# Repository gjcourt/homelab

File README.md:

<!-- readme-type: infra -->
# Homelab

GitOps for a 4-node Talos Kubernetes homelab cluster, reconciled by Flux CD

Running a cluster by hand invites config drift and leaves no record of what
changed or why. This repo is the single source of truth for the
`melodic-muse` Talos cluster: every app, controller, and cluster config lives
here as a Kustomize base, overlay, or Helm release. Flux CD reconciles
`master` into the cluster on a 10-minute interval (or on demand), so a merged
PR is the only way anything reaches production.

**Status:** in daily use — this is the live source of truth for the
`melodic-muse` cluster; Flux reconciles `master` continuously, with commits
landing as recently as 2026-09-29.

## Layout

```text
apps/       Kustomize bases + staging/production overlays, one directory per app
infra/      controllers (HelmReleases) and the configs they depend on
clusters/   Flux Kustomization entrypoints
hosts/      compose files, scripts, and docs for hosts outside Kubernetes (hestia, alcatraz, ...)
images/     Dockerfiles for the images this repo builds and publishes to ghcr.io
firmware/   ESPHome configs for IR blasters and sensors
docs/       architecture, runbooks, plans, incident postmortems
scripts/    repo maintenance and host-ops tooling
renovate/   Renovate dependency-update config
```

Current app and infra inventory: [apps/README.md](apps/README.md),
[infra/README.md](infra/README.md). Current cluster state, in-flight work, and
known issues: [docs/STATUS.md](docs/STATUS.md).

## Making a change

1. Branch from `master`: `git checkout master && git pull && git checkout -b <type>/<description>`.
2. Edit `apps/`, `infra/`, `docs/`, or `scripts/`, and validate locally (see Development below).
3. Push and open a PR. CI rebuilds the `staging` branch (`master` plus every
   open, mergeable PR whose checks pass) and deploys it to the `-stage` namespaces, so you can check the
   change against the real cluster before it merges.
4. Merging to `master` deploys to production on Flux's next reconcile, or
   force it with `flux reconcile kustomization apps-production -n flux-system`.

Secrets are SOPS-encrypted before commit and decrypted in-cluster by Flux;
never commit a plaintext secret. Full walkthrough, including adding a new app
and rolling back:
[docs/operations/making-changes.md](docs/operations/making-changes.md).

## Development

```bash
make test                                    # kustomize build + kubeconform (apps/staging, apps/production, infra/*) + yamlfmt check
make lint                                    # yamllint (.yamllint) + shellcheck on scripts/*.sh
(cd scripts/plans-index && go run . -check)  # verify docs/plans frontmatter matches the generated index
```

Conventions, invariants, and the full command reference:
[AGENTS.md](AGENTS.md).

## License

[MIT](LICENSE)

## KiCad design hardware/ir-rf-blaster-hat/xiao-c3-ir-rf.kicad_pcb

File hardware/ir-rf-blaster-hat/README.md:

# XIAO ESP32-C3 IR + RF Blaster Hat — 4-layer, routed

A XIAO-carrier "hat": the XIAO ESP32-C3 sockets into female headers (Seeed's **official
XIAO-ESP32-C3-DIP** footprint); the board carries a **triple-IR-LED blaster** (MOSFET-driven)
**and a CC1101 sub-GHz RF transmitter** (TX-only). IR LEDs are THT (hand-soldered, better
range); everything else SMD for JLCPCB assembly. The CC1101 is a socketed **EBYTE E07-M1101D**
module.

**Status (2026-07-14): 4-layer, fully routed, DRC-clean, fab-ready.** Generated headlessly
(`generate_pcb.py`, kiutils) + zone-filled + validated with `kicad-cli` (KiCad 9): **DRC 0
errors, 0 unconnected**. Board is **23 × 54 mm**. Gerbers/drill in
[`ir-rf-gerbers.zip`](ir-rf-gerbers.zip); renders [`ir-rf-top.png`](ir-rf-top.png) /
[`ir-rf-bottom.png`](ir-rf-bottom.png); module orientation [`e07-orientation.svg`](e07-orientation.svg).

## Floorplan

```
        NORTH (top)
   ┌──────────────────┐
   │  D1   D2   D3     │  3× 940 nm IR LED (THT), aimed north/off the top edge
   │  R  Q1  R   caps  │  MOSFET driver row
   │ ┌──────────────┐  │
USB┤ │ XIAO (front) │  │  XIAO horizontal — USB-C exits the WEST edge
   │ └──────────────┘  │
   │   [E07 on BACK]   │  E07-M1101D on a 2×4 female socket, flipped to B.Cu;
   │        ││         │  15×30 mm module body lies over the XIAO back and
   │        ▼▼         │  extends SOUTH — SMA/antenna off the south edge.
   └────────╨╨────────┘
        SOUTH (antenna)
```

- **XIAO** is on the **front** (Seeed official XIAO-ESP32-C3-DIP footprint), rotated horizontal
  (rot 180) so **USB-C exits the west edge**; the two 7-pin rows run E-W, **15.24 mm apart**
  (real Seeed pitch). NORTH row = 5V/GND/3V3 + D10/D9/D8/D7; SOUTH row = D0–D6.
- **E07-M1101D CC1101** is on the **back**, on a **swappable 2×4 female socket**. Per the
  CDEBYTE datasheet the 2×4 header runs **4-across the module's 15 mm width**; the 30 mm body
  + SMA connector extend perpendicular to it, so with the header at the north end the
  **antenna points south, off the board edge**. An **all-layer copper keepout** clears the
  planes under the RF/antenna region (y 46–54).

## Frequency & the swappable socket

The **CC1101 chip** is multi-band (300–348 / 387–464 / 779–928 MHz), but any physical
**module** is impedance-matched + antenna-tuned to **one** band. The **E07-M1101D is a 433 MHz
module** (covers ~387–464 MHz) — the common band for US/EU fixed-code outlets, doorbells, many
fan remotes. 315 MHz gear (some garage openers/older remotes) or 868/915 MHz needs a
differently-tuned module.

The board is deliberately **band-agnostic**: the CC1101 slot is a plain 8-pin 2×4 socket, so
any same-pinout CC1101 module (or an SMA E07 with a swapped antenna) drops in. Pick the module
for your band; the PCB doesn't change.

## Stackup (4-layer)

| Layer      | Use                                                       |
| ---------- | --------------------------------------------------------- |
| **F.Cu**   | components + signals (IR section, N-row SPI, +3V3)         |
| **In1.Cu** | **GND plane** (solid) — clean return for the IR pulses    |
| **In2.Cu** | **+5V plane** — LED current                               |
| **B.Cu**   | signals (S-row SPI, GDO2 dogleg, gate)                    |

GND and +5V go to their planes via stitching vias (through-vias; the opposite plane's zone
clears around each). Only `+3V3` and the logic signals are routed as tracks. The E07 socket's
GND/VCC pins are THT and land directly on the planes.

## Pin maps

**XIAO ESP32-C3** (official pad numbers) — the E07 **north row** (odd pins, datasheet order)
fans from the XIAO **north** row; the **south row** (even pins) from the XIAO **south** row.
`MISO` is the one north-row net fed from the south (a clean east-side dogleg). **All three
strapping pins are left spare** — D0/GPIO2 (pad 1), D8/GPIO8 (pad 9), D9/GPIO9 (pad 10). `IR_TX`
is on **D1/GPIO3** (non-strapping): D0 was avoided because the 10 kΩ gate pulldown would drag
GPIO2 low at reset (~0.6 V through the ~45 kΩ internal pull-up), against ESP32-C3 guidance.

| Net      | XIAO pin | GPIO | pad # | → E07 pin      |
| -------- | -------- | ---- | ----- | -------------- |
| IR_TX    | D1       | 3    | 2     | (to MOSFET)    |
| CC_GDO0  | D10      | 10   | 11    | 3 (N row)      |
| CC_SCK   | D7       | 20   | 8     | 5 (N row)      |
| CC_MISO  | D6       | 21   | 7     | 7 (N, dogleg)  |
| CC_CSN   | D2       | 4    | 3     | 4 (S row)      |
| CC_MOSI  | D3       | 5    | 4     | 6 (S row)      |
| CC_GDO2  | D4       | 6    | 5     | 8 (S row)      |
| +3V3     | 3V3      | —    | 12    | 2 (VCC)        |
| GND      | GND      | —    | 13    | 1              |
| +5V      | VBUS     | —    | 14    | —              |

Power: IR LEDs → **5V (VBUS)**; CC1101 → **3V3**; common GND. D0/D5/D8/D9 (pads 1/6/9/10) spare.

**Hand-solder polarity (THT):**
- **D1–D3 IR LEDs** — footprint **pad 1 (square, west, flat-silk side) = CATHODE**; pad 2
  (round, east) = anode = +5 V. Solder each LED with its **flat / short lead (cathode) to the
  square pad**. (The cathode goes to the current-limit resistor → MOSFET; the anode to +5 V.)
- **A1 XIAO** and **M1 E07** — keyed by pad 1 (square) on their footprints; match pin 1.

**E07-M1101D socket (M1, 2×4 female)** — **fixed CDEBYTE pinout**, the module plugs straight in:

```
  1 GND    2 VCC(3V3)
  3 GDO0   4 CSN
  5 SCK    6 MOSI
  7 MISO   8 GDO2
```

> ⚠️ E07 logic is **3.3 V** — the datasheet warns 5 V TTL "may be at risk of burning down."
> The XIAO drives it at 3.3 V; keep it off VBUS.

## BOM

| Ref     | Part                | Value/MPN            | Pkg    | Mount | Footprint                  |
| ------- | ------------------- | -------------------- | ------ | ----- | -------------------------- |
| Q1      | N-ch MOSFET         | AO3400A (C20917)     | SOT-23 | SMT   | `SOT-23`                   |
| D1–D3   | 940 nm IR LED       | TSAL6400             | 5 mm   | THT   | `LED_D5.0mm`               |
| R1–R3   | Res (LED limit)     | 15 Ω                 | 1206   | SMT   | `R_1206_3216Metric`        |
| R4      | Res (gate)          | 100 Ω                | 0603   | SMT   | `R_0603_1608Metric`        |
| R5      | Res (pulldown)      | 10 kΩ                | 0603   | SMT   | `R_0603_1608Metric`        |
| C1,C3   | Cap                 | 100 nF               | 0603   | SMT   | `C_0603_1608Metric`        |
| C2      | Cap (IR bulk)       | 22 µF                | 0805   | SMT   | `C_0805_2012Metric`        |
| C4      | Cap (RF bulk)       | 10 µF                | 0805   | SMT   | `C_0805_2012Metric`        |
| M1      | **E07-M1101D** hdr  | 2×4 socket, 2.54 mm  | THT    | hand  | `PinSocket_2x04_P2.54mm`   |
| A1      | XIAO ESP32-C3 socket| 2×7 female, 2.54 mm  | THT    | hand  | `XIAO-ESP32-C3-DIP` (Seeed)|

Module (not on the PCB BOM): **EBYTE E07-M1101D** (or E07-M1101D-SMA for an external antenna),
433 MHz, LCSC C108549 / Amazon.

## Before ordering (KiCad GUI)

- **Footprint:** now Seeed's official `XIAO-ESP32-C3-DIP` (15.24 mm rows) — the footprint's own
  silk is stripped in the generator (it overhangs the USB end and crosses its castellated pads);
  pads + our labels remain.
- **Back-side stack (confirmed OK):** the E07 socket pins protrude ~1 mm through-hole under the
  XIAO — clears fine. The 30 mm module body overhangs the south edge slightly; the SMA/antenna
  sits in free air beyond the board.
- Optional: a final 3D view before fab.

## Regenerate / validate / order (headless)

```sh
# 1. generate the board (native, kiutils) - writes zones UNFILLED
python3 generate_pcb.py footprints xiao-c3-ir-rf.kicad_pcb

# 2. fill zones + validate + export (KiCad 9; amd64 image on Apple Silicon)
docker run --rm --platform linux/amd64 -v "$PWD:/w" -w /w kicad/kicad:9.0 sh -c '
  python3 /w/fill_zones.py xiao-c3-ir-rf.kicad_pcb xiao-c3-ir-rf.kicad_pcb
  kicad-cli pcb drc xiao-c3-ir-rf.kicad_pcb
  kicad-cli pcb export gerbers -o g/ xiao-c3-ir-rf.kicad_pcb
  kicad-cli pcb export drill   -o g/ xiao-c3-ir-rf.kicad_pcb'
```

> **Toolchain note:** `pcbnew` Python scripting crashes under amd64 emulation on Apple Silicon
> in `FootprintLoad` (`malloc(): unaligned tcache chunk`) — so the board is *generated* with
> **kiutils** (native, pure-Python) and *zone-filled* with **`pcbnew.LoadBoard`** (which does
> NOT crash), then `kicad-cli` runs DRC/export. `footprints/` holds the KiCad-9 footprints the
> generator places (offline-reproducible).
>
> One headless gotcha baked into the generator: kicad-cli places a **B.Cu** THT footprint's
> pads at the plain rotated local coords (no X-mirror), so `abspad()` must **not** mirror — the
> E07 even/odd pins land on the south/north rows accordingly.

## Firmware (ESPHome)

`../../firmware/esphome/ir-rf-blaster-xiao-c3.yaml`: `remote_transmitter` (IR) — note IR_TX is
now **GPIO3 (D1)** (was GPIO4); update the YAML pin. The CC1101 needs an **external component**
(SPI init + GDO0 OOK bridge) — a known community pattern, not stock ESPHome. Match the pin map
above: **SCK=GPIO20, MISO=GPIO21, MOSI=GPIO5, CSN=GPIO4, GDO0=GPIO10, GDO2=GPIO6**.

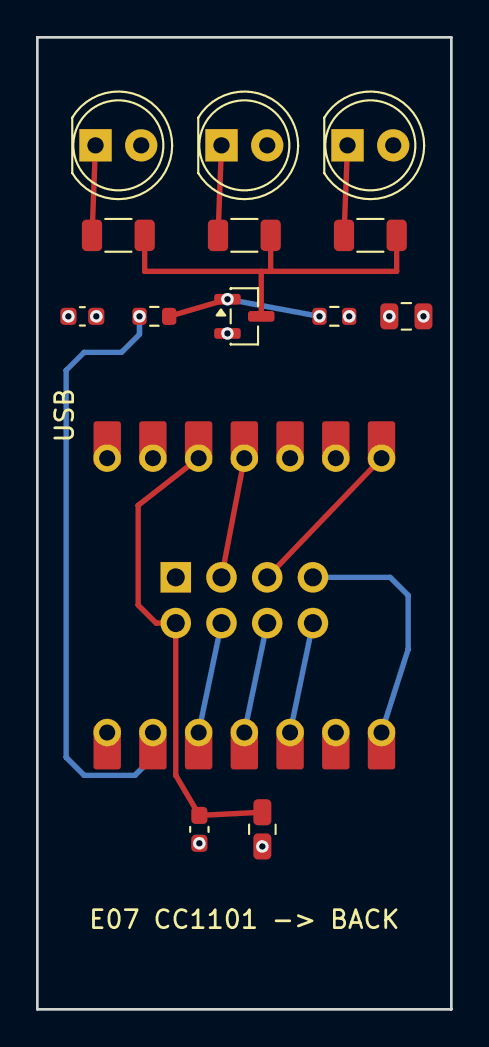
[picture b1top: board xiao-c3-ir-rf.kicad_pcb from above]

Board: 4 copper layers, 23.0 x 54.0 mm, 15 parts (1 on the bottom side), 15 nets.

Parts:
A1: XIAO_ESP32C3; XIAO-ESP32-C3-DIP
C1, C3: 100nF; C_0603_1608Metric
C2: 22uF; C_0805_2012Metric
C4: 10uF; C_0805_2012Metric
D1, D2, D3: 940nm; LED_D5.0mm
M1: E07-M1101D; PinSocket_2x04_P2.54mm_Vertical
Q1: AO3400A; SOT-23
R1, R2, R3: 15R; R_1206_3216Metric
R4: 100R; R_0603_1608Metric
R5: 10k; R_0603_1608Metric

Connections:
+3V3: A1.12, C3.1, C4.1, M1.2
+5V: A1.14, C1.1, C2.1, D1.2, D2.2, D3.2
CC_CSN: A1.3, M1.4
CC_GDO0: A1.11, M1.3
CC_GDO2: A1.5, M1.8
CC_MISO: A1.7, M1.7
CC_MOSI: A1.4, M1.6
CC_SCK: A1.8, M1.5
GND: A1.13, C1.2, C2.2, C3.2, C4.2, M1.1, Q1.2, R5.2
IR_TX: A1.2, R4.1
LED1_K: D1.1, R1.1
LED2_K: D2.1, R2.1
LED3_K: D3.1, R3.1
Q_DRAIN: Q1.3, R1.2, R2.2, R3.2
Q_GATE: Q1.1, R4.2, R5.1
